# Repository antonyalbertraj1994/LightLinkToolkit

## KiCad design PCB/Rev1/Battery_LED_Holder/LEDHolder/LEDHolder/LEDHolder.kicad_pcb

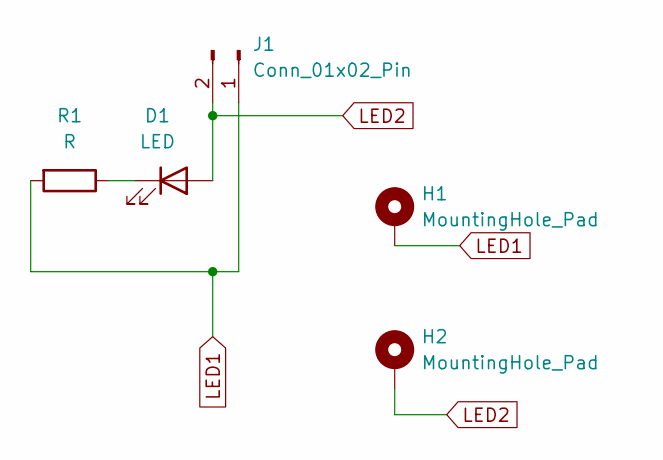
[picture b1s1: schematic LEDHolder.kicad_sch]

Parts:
D1: LED; LED_0805_2012Metric_Pad1.15x1.40mm_HandSolder
H1, H2: MountingHole_Pad; MT_Hole
J1: Conn_01x02_Pin; PinHeader_1x02_P2.54mm_Vertical
R1: R; R_0603_1608Metric_Pad0.98x0.95mm_HandSolder

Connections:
LED1: H1.1, J1.1, R1.2
LED2: D1.2 (A), H2.1, J1.2
unnamed: D1.1 (K), R1.1

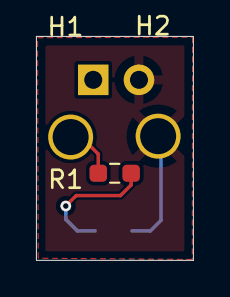
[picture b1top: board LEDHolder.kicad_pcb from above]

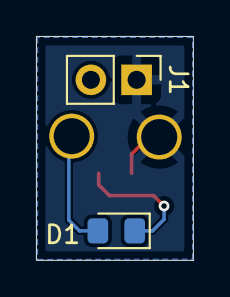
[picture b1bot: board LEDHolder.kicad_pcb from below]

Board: 2 copper layers, 8.7 x 12.4 mm, 5 parts (2 on the bottom side), 3 nets.

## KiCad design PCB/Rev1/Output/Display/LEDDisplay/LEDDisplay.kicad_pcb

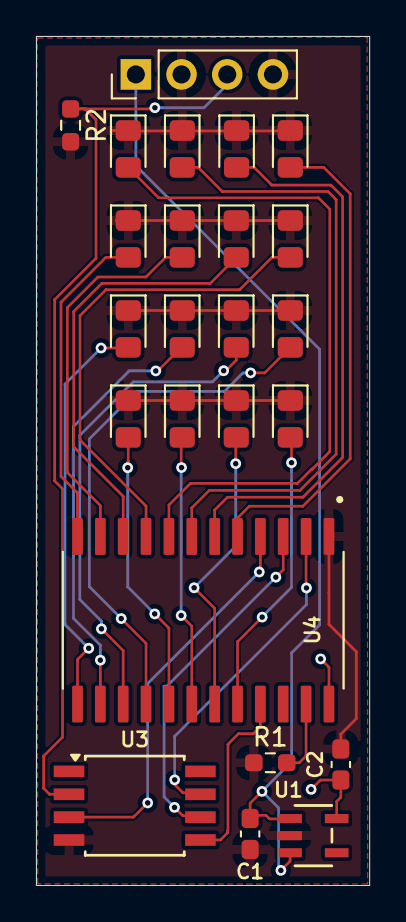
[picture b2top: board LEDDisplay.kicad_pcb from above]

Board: 2 copper layers, 18.5 x 47.2 mm, 24 parts (0 on the bottom side), 25 nets.

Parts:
C1, C2: C; C_0603_1608Metric_Pad1.08x0.95mm_HandSolder
D1, D2, D3, D4, D5, D6, D7, D8, D9, D10, D11, D12, D13, D14, D15, D16: LED; LED_0805_2012Metric_Pad1.15x1.40mm_HandSolder
J3: Conn_01x04_Pin; PinHeader_1x04_P2.54mm_Vertical
R1, R2: R; R_0603_1608Metric_Pad0.98x0.95mm_HandSolder
U1: MIC5504; SOT-23-5_MC_MCH
U3: ATtiny85; SOIC-8W_5.3x5.3mm_P1.27mm
U4: STP16CP05MTR; SOIC127P1032X265-24N

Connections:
BPW34_1: J3.3, R2.1, U3.2 (XTAL1/PB3)
CLK: U3.6 (PB1), U4.3 (CLK)
DATA: U3.7 (PB2), U4.2 (SDI)
GND: C1.2, C2.2, D1.1 (K), D2.1 (K), D3.1 (K), D4.1 (K), D5.1 (K), D6.1 (K), D7.1 (K), D8.1 (K), D9.1 (K), D10.1 (K), D11.1 (K), D12.1 (K), D13.1 (K), D14.1 (K), D15.1 (K), D16.1 (K), J3.2, J3.4, R1.1, R2.2, U1.2 (GND), U3.4 (GND), U4.1 (GND)
L1: D1.2 (A), U4.5 (~OUT0)
L2: D2.2 (A), U4.6 (~OUT1)
L3: D3.2 (A), U4.7 (~OUT2)
L4: D4.2 (A), U4.8 (~OUT3)
L5: D5.2 (A), U4.9 (~OUT4)
L6: D6.2 (A), U4.10 (~OUT5)
L7: D7.2 (A), U4.11 (~OUT6)
L8: D8.2 (A), U4.12 (~OUT7)
L9: D9.2 (A), U4.13 (~OUT8)
L10: D10.2 (A), U4.14 (~OUT9)
L11: D11.2 (A), U4.15 (~OUT10)
L12: D12.2 (A), U4.16 (~OUT11)
L13: D13.2 (A), U4.17 (~OUT12)
L14: D14.2 (A), U4.18 (~OUT13)
L15: D15.2 (A), U4.19 (~OUT14)
L16: D16.2 (A), U4.20 (~OUT15)
LE: U3.3 (XTAL2/PB4), U4.4 (LE/DM1)
unnamed: R1.2, U4.23 (R-EXT)
OE: U3.5 (AREF/PB0), U4.21 (~OE/DM2)
VCC: C1.1, J3.1, U1.1 (VIN), U1.3 (EN)
VDD_3.3V: C2.1, U1.5 (VOUT), U4.24 (VDD)

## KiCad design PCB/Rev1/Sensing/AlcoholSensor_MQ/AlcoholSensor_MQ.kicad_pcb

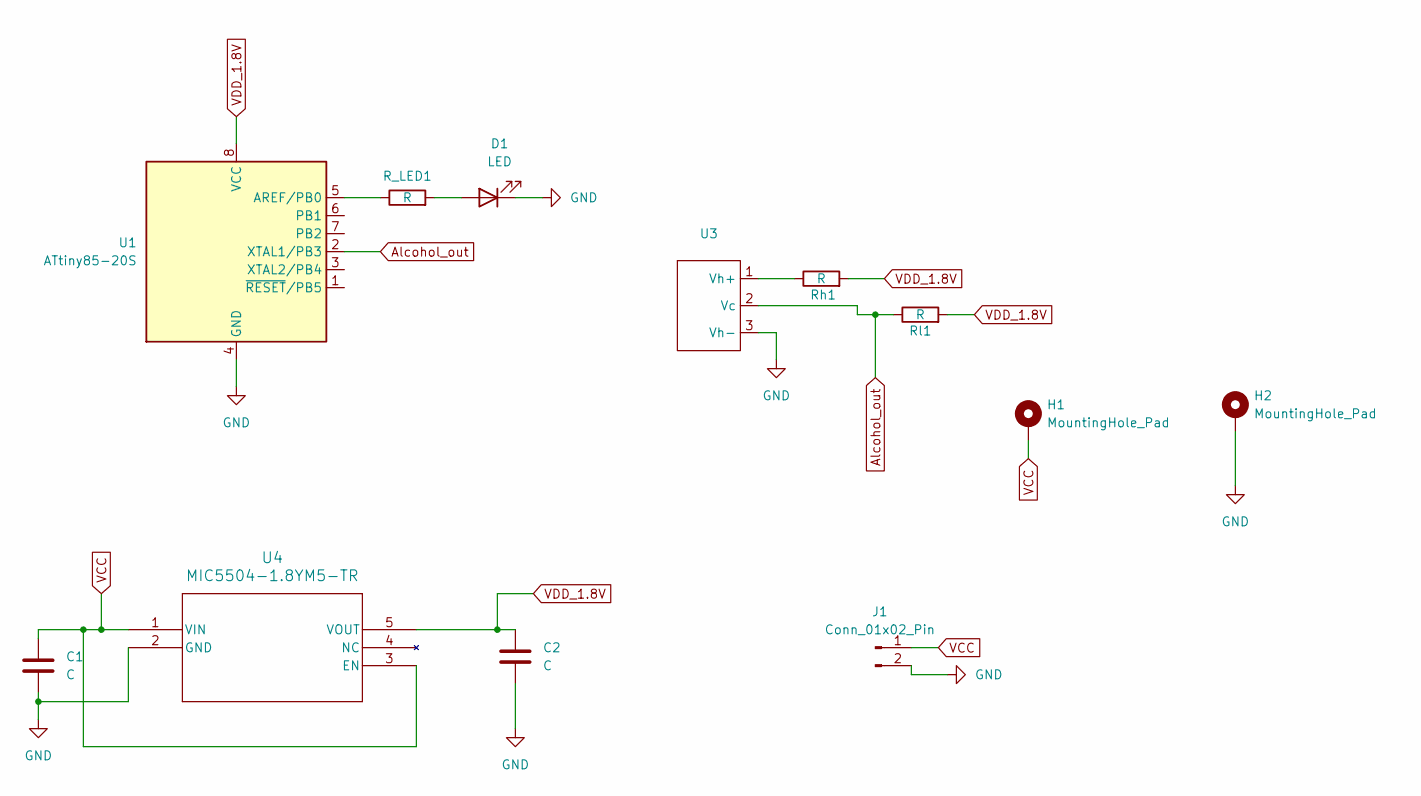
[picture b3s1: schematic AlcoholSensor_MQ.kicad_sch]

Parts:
C1, C2: C; C_0603_1608Metric_Pad1.08x0.95mm_HandSolder
D1: LED; LED_0805_2012Metric_Pad1.15x1.40mm_HandSolder
H1, H2: MountingHole_Pad; MT_Hole
J1: Conn_01x02_Pin; PinHeader_1x02_P2.54mm_Vertical
R_LED1: R; R_0603_1608Metric_Pad0.98x0.95mm_HandSolder
Rh1: R; R_0603_1608Metric_Pad0.98x0.95mm_HandSolder
Rl1: R; R_0603_1608Metric_Pad0.98x0.95mm_HandSolder
U1: ATtiny85-20S; SOIC-8W_5.3x5.3mm_P1.27mm
U3: MQ303
U4: MIC5504-1.8YM5-TR; SOT23-5LD-PL-1_MCH

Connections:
Alcohol_out: Rl1.1, U1.2 (XTAL1/PB3), U3.2 (Vc)
GND: C1.2, C2.2, D1.1 (K), H2.1, J1.2, U1.4 (GND), U3.3 (Vh-), U4.2 (GND)
unnamed: D1.2 (A), R_LED1.2
unnamed: R_LED1.1, U1.5 (AREF/PB0)
unnamed: Rh1.1, U3.1 (Vh+)
VCC: C1.1, H1.1, J1.1, U4.1 (VIN), U4.3 (EN)
VDD_1.8V: C2.1, Rh1.2, Rl1.2, U1.8 (VCC), U4.5 (VOUT)

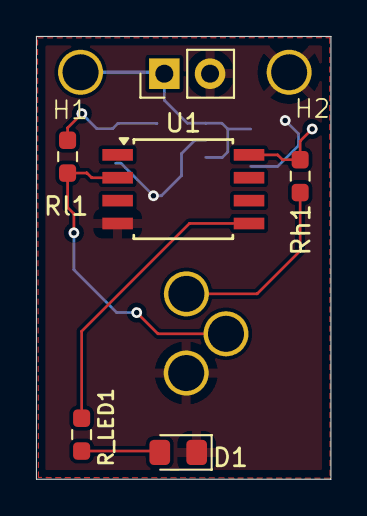
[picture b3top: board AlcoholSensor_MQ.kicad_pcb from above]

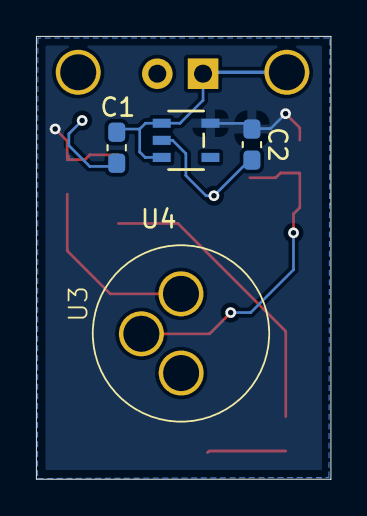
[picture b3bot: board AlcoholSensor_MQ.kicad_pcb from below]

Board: 2 copper layers, 16.4 x 24.6 mm, 12 parts (4 on the bottom side), 7 nets.

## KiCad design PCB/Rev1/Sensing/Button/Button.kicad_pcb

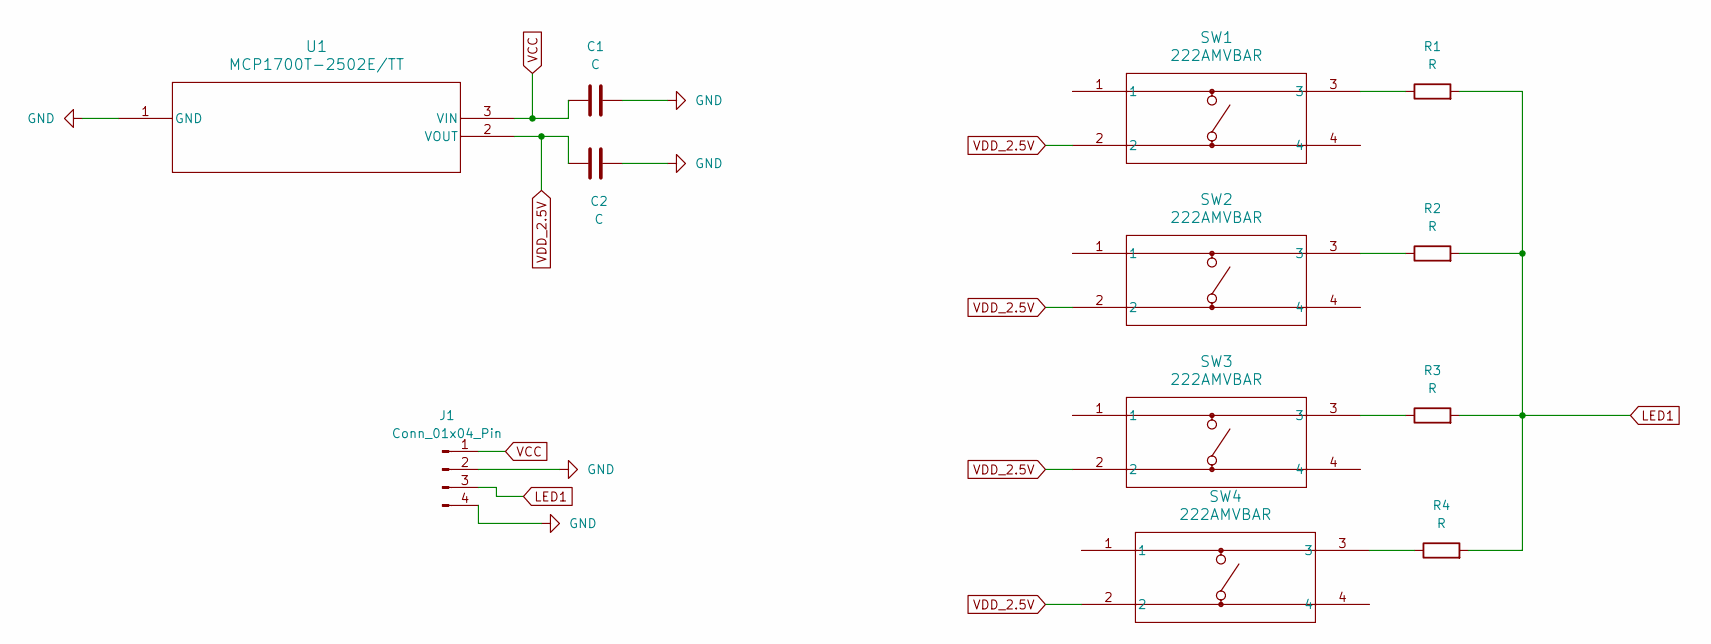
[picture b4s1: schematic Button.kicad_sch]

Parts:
C1, C2: C; C_0603_1608Metric
J1: Conn_01x04_Pin; PinHeader_1x04_P2.54mm_Vertical
R1, R2, R3, R4: R; R_0603_1608Metric
SW1, SW2, SW3, SW4: 222AMVBAR; SO4_222A-M-V-B_CTS
U1: MCP1700T-2502E/TT; SOT-23_MC_MCH

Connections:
GND: C1.2, C2.2, J1.2, J1.4, U1.1 (GND)
LED1: J1.3, R1.2, R2.2, R3.2, R4.2
unnamed: R1.1, SW1.3
unnamed: R2.1, SW2.3
unnamed: R3.1, SW3.3
unnamed: R4.1, SW4.3
VCC: C1.1, J1.1, U1.3 (VIN)
VDD_2.5V: C2.1, SW1.2, SW2.2, SW3.2, SW4.2, U1.2 (VOUT)

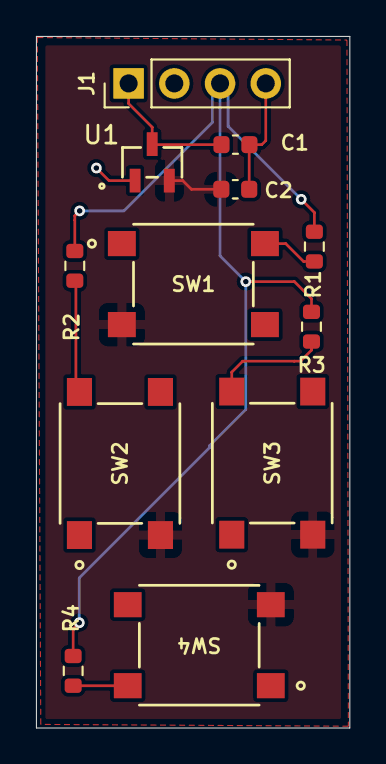
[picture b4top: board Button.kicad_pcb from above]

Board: 2 copper layers, 17.4 x 38.4 mm, 12 parts (0 on the bottom side), 8 nets.

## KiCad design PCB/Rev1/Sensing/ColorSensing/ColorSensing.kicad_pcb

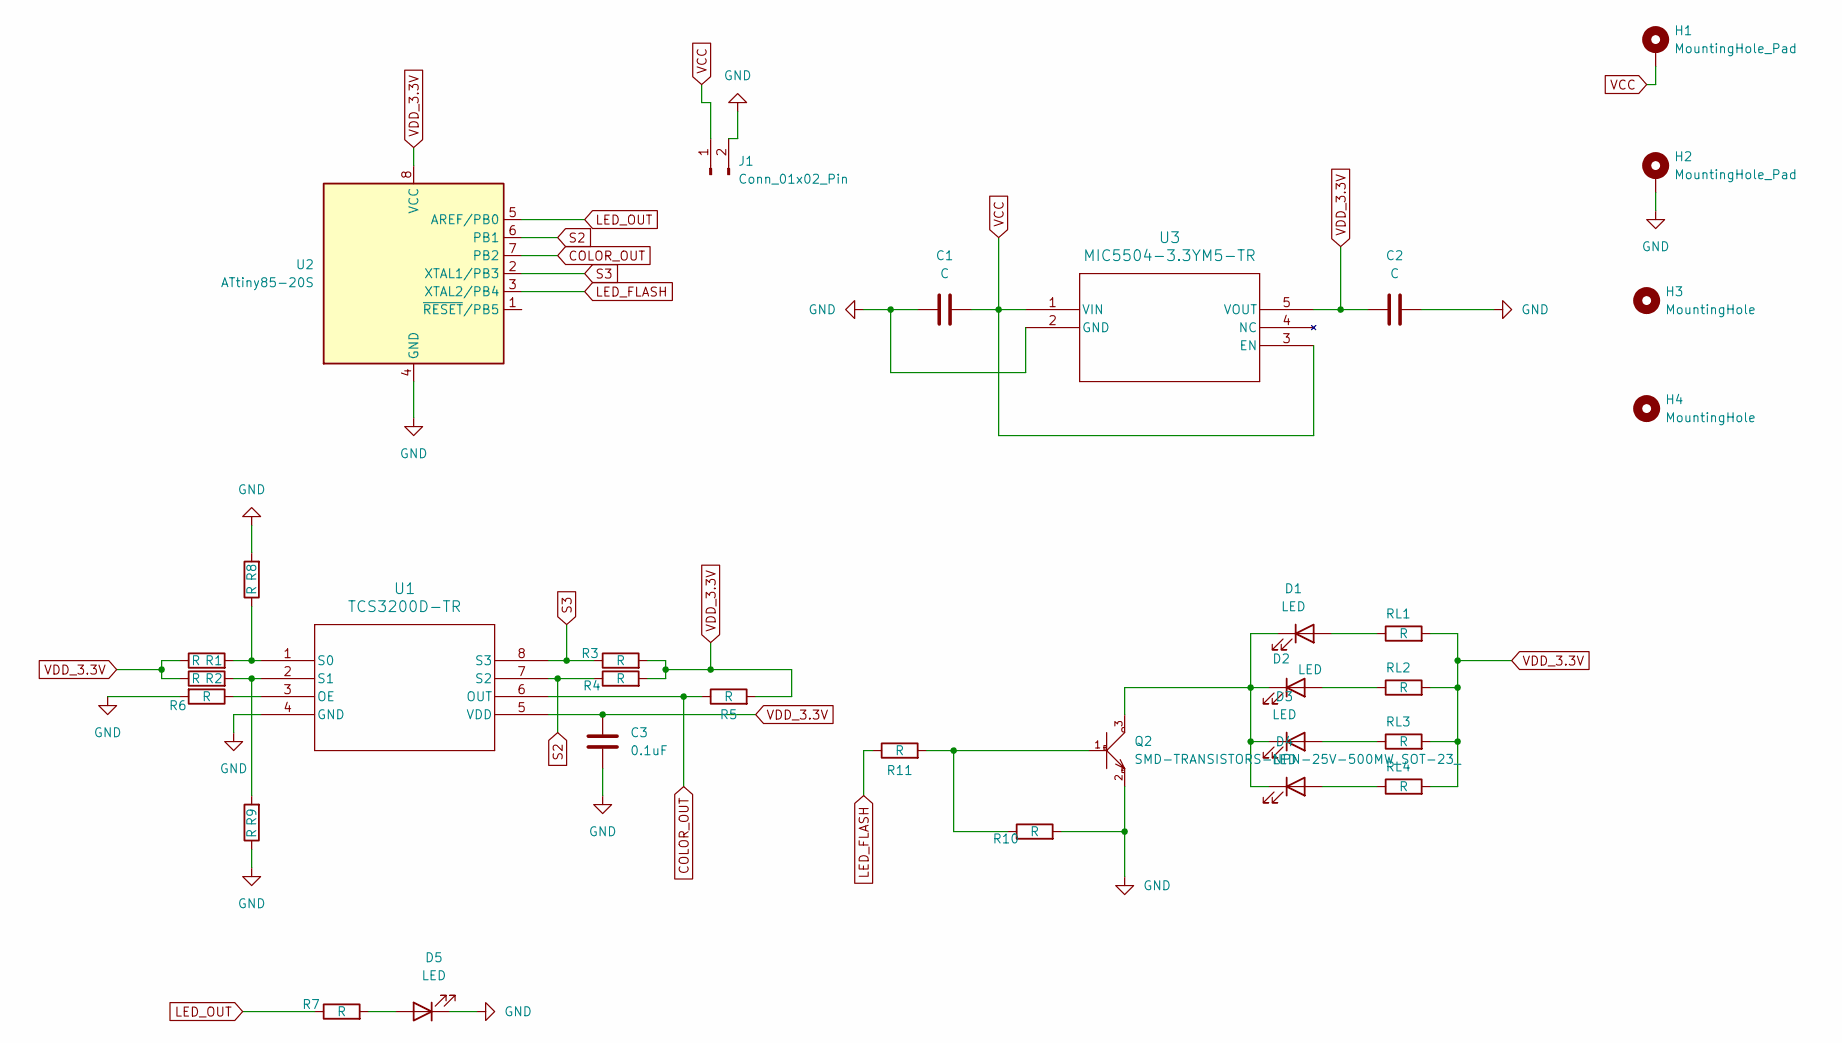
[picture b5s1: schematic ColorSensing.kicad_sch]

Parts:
C1, C2: C; C_0603_1608Metric_Pad1.08x0.95mm_HandSolder
C3: 0.1uF; C_0603_1608Metric_Pad1.08x0.95mm_HandSolder
D1, D2, D3, D4: LED; LED_D5.0mm
D5: LED; LED_0805_2012Metric_Pad1.15x1.40mm_HandSolder
H1, H2: MountingHole_Pad; MT_Hole
H3, H4: MountingHole; MT_Hole
J1: Conn_01x02_Pin; PinHeader_1x02_P2.54mm_Vertical
Q2: SMD-TRANSISTORS-NPN-25V-500MW_SOT-23_; SOT-23; MPN S8050
R1, R2, R3, R4, R5, R6, R7, R8, R9, R10, R11: R; R_0603_1608Metric_Pad0.98x0.95mm_HandSolder
RL1, RL2, RL3, RL4: R; R_0603_1608Metric_Pad0.98x0.95mm_HandSolder
U1: TCS3200D-TR; SO_3200D-TR_AMS
U2: ATtiny85-20S; SOIC-8W_5.3x5.3mm_P1.27mm
U3: MIC5504-3.3YM5-TR; SOT-23-5_MC_MCH

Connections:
COLOR_OUT: R5.1, U1.6 (OUT), U2.7 (PB2)
GND: C1.1, C2.2, C3.1, D5.1 (K), H2.1, J1.2, Q2.2, R6.2, R8.2, R9.1, R10.2, U1.4 (GND), U2.4 (GND), U3.2 (GND)
LED_FLASH: R11.1, U2.3 (XTAL2/PB4)
LED_OUT: R7.1, U2.5 (AREF/PB0)
unnamed: D1.2 (A), RL1.1
unnamed: D1.1 (K), D2.1 (K), D3.1 (K), D4.1 (K), Q2.3
unnamed: D2.2 (A), RL2.1
unnamed: D3.2 (A), RL3.1
unnamed: D4.2 (A), RL4.1
unnamed: D5.2 (A), R7.2
unnamed: Q2.1, R10.1, R11.2
unnamed: R6.1, U1.3 (OE)
unnamed: R1.2, R8.1, U1.1 (S0)
unnamed: R2.2, R9.2, U1.2 (S1)
S2: R4.1, U1.7 (S2), U2.6 (PB1)
S3: R3.1, U1.8 (S3), U2.2 (XTAL1/PB3)
VCC: C1.2, H1.1, J1.1, U3.1 (VIN), U3.3 (EN)
VDD_3.3V: C2.1, C3.2, R1.1, R2.1, R3.2, R4.2, R5.2, RL1.2, RL2.2, RL3.2, RL4.2, U1.5 (VDD), U2.8 (VCC), U3.5 (VOUT)

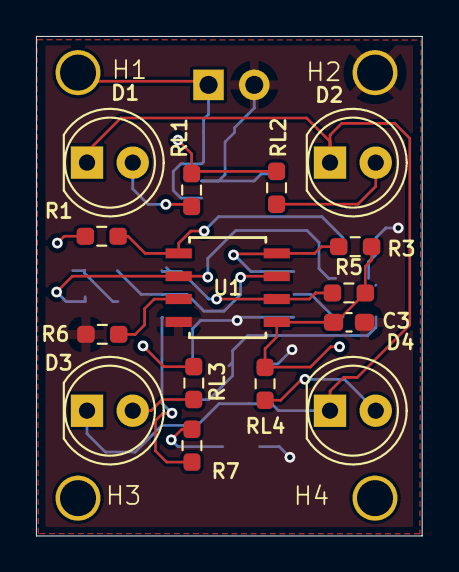
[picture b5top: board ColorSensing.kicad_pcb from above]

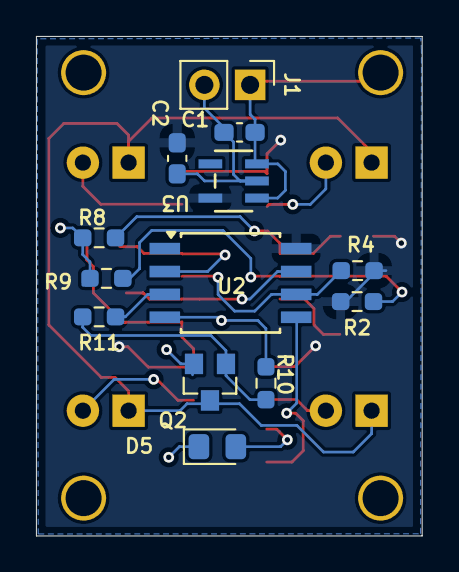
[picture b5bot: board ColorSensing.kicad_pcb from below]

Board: 2 copper layers, 21.4 x 27.8 mm, 32 parts (13 on the bottom side), 18 nets.

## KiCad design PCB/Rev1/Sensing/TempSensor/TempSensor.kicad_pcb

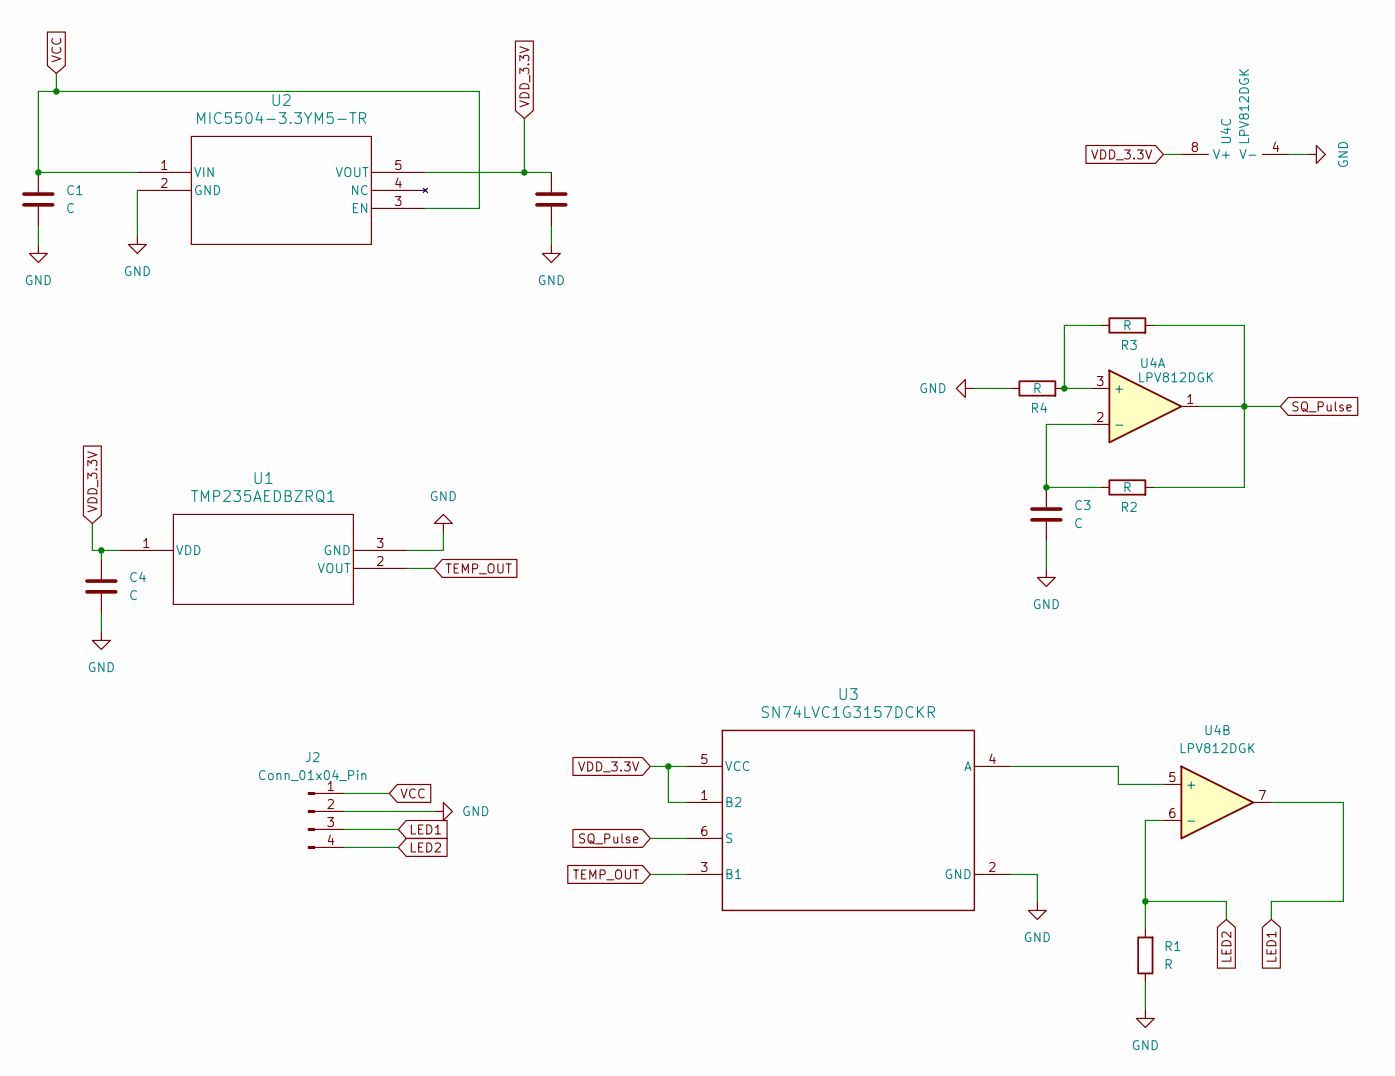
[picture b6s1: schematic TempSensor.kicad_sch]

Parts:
C1, C2, C3, C4: C; C_0603_1608Metric_Pad1.08x0.95mm_HandSolder
J2: Conn_01x04_Pin; PinHeader_1x04_P2.54mm_Vertical
R1, R2, R3, R4: R; R_0603_1608Metric_Pad0.98x0.95mm_HandSolder
U1: TMP235AEDBZRQ1; SOT-23_DBZ_TEX
U2: MIC5504-3.3YM5-TR; SOT-23-5_MC_MCH
U3: SN74LVC1G3157DCKR; DBV6
U4: LPV812DGK; VSSOP-8_3.0x3.0mm_P0.65mm

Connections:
GND: C1.2, C2.2, C3.2, C4.2, J2.2, R1.1, R4.1, U1.3 (GND), U2.2 (GND), U3.2 (GND), U4.4 (V-)
LED1: J2.3, U4.7
LED2: J2.4, R1.2, U4.6 (-)
unnamed: U3.4 (A), U4.5 (+)
unnamed: R3.1, R4.2, U4.3 (+)
unnamed: C3.1, R2.1, U4.2 (-)
SQ_Pulse: R2.2, R3.2, U3.6 (S), U4.1
TEMP_OUT: U1.2 (VOUT), U3.3 (B1)
VCC: C1.1, J2.1, U2.1 (VIN), U2.3 (EN)
VDD_3.3V: C2.1, C4.1, U1.1 (VDD), U2.5 (VOUT), U3.1 (B2), U3.5 (VCC), U4.8 (V+)

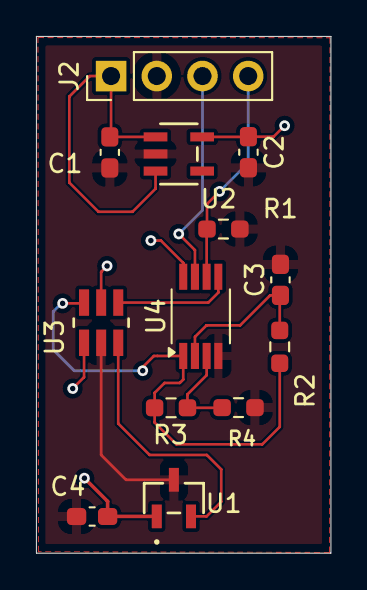
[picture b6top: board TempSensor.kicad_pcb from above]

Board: 2 copper layers, 16.4 x 28.7 mm, 13 parts (0 on the bottom side), 10 nets.

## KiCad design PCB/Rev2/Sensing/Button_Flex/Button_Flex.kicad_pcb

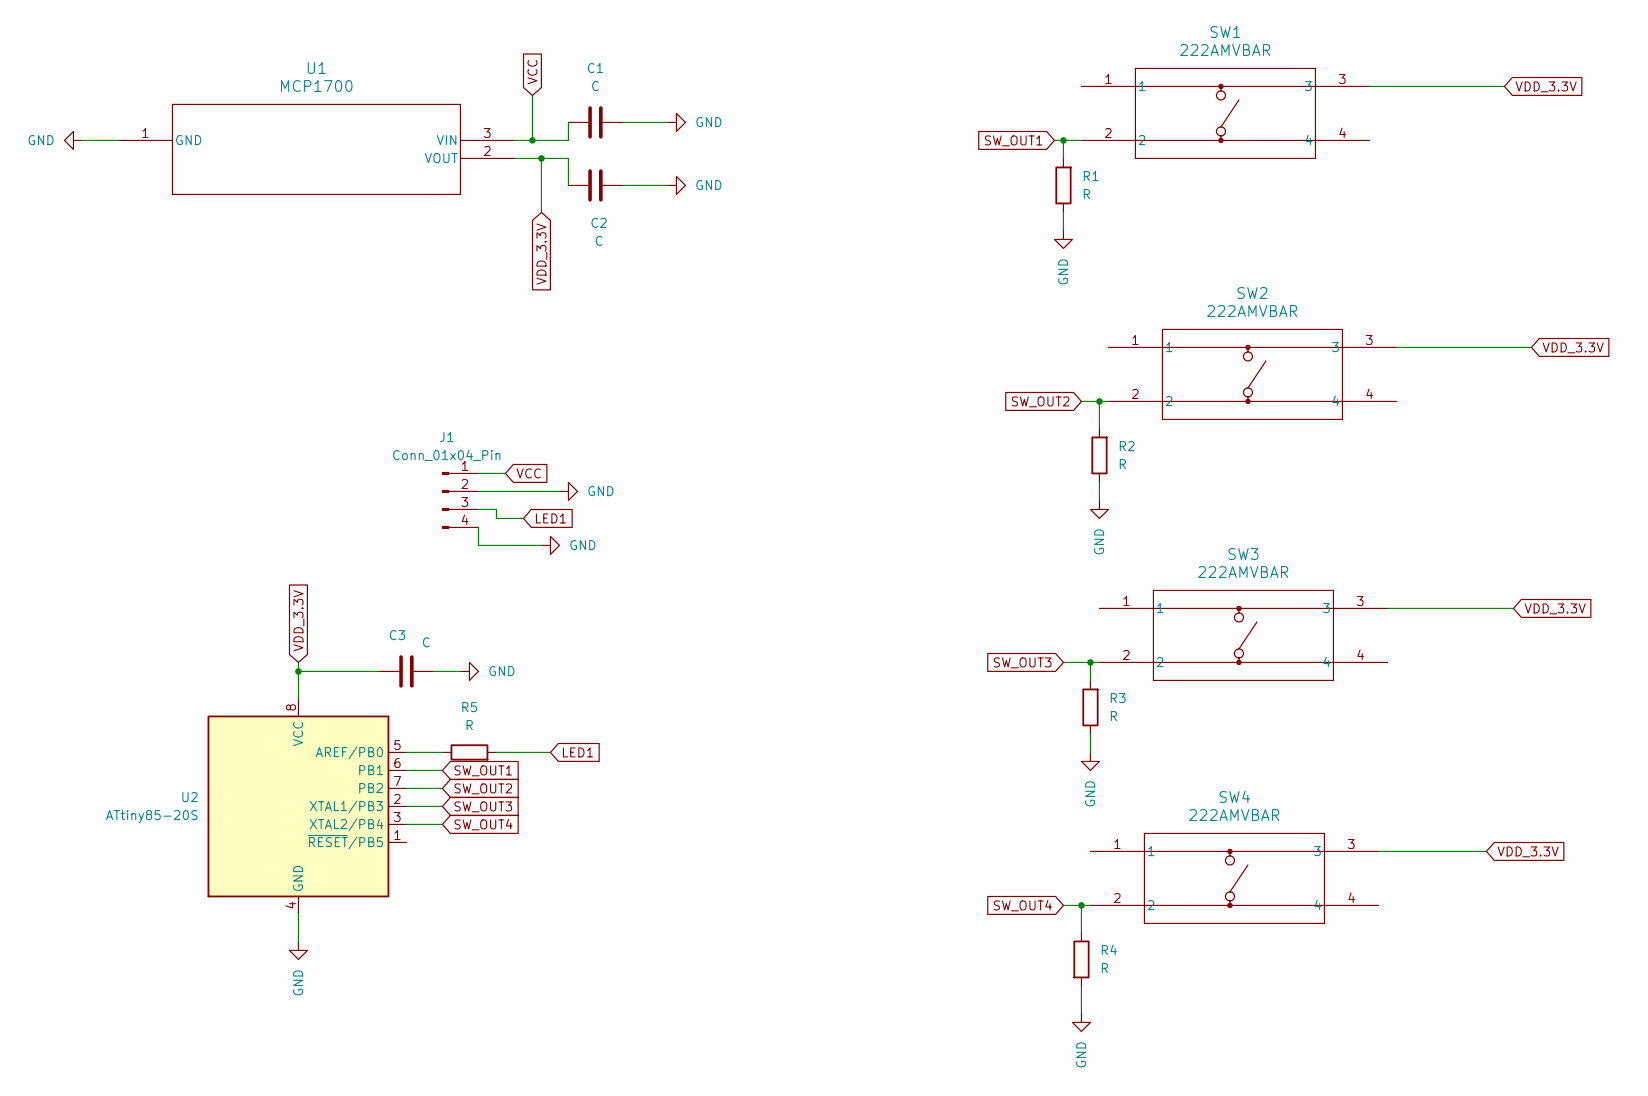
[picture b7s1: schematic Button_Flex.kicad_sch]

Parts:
C1, C2, C3: C; C_0603_1608Metric
J1: Conn_01x04_Pin; PinHeader_1x04_P2.54mm_Vertical
R1, R2, R3, R4, R5: R; R_0603_1608Metric
SW1, SW2, SW3, SW4: 222AMVBAR; SO4_222A-M-V-B_CTS
U1: MCP1700; SOT-23_MC_MCH
U2: ATtiny85-20S; SOIC-8W_5.3x5.3mm_P1.27mm

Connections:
GND: C1.2, C2.2, C3.2, J1.2, J1.4, R1.1, R2.1, R3.1, R4.2, U1.1 (GND), U2.4 (GND)
LED1: J1.3, R5.2
unnamed: R5.1, U2.5 (AREF/PB0)
SW_OUT1: R1.2, SW1.2, U2.6 (PB1)
SW_OUT2: R2.2, SW2.2, U2.7 (PB2)
SW_OUT3: R3.2, SW3.2, U2.2 (XTAL1/PB3)
SW_OUT4: R4.1, SW4.2, U2.3 (XTAL2/PB4)
VCC: C1.1, J1.1, U1.3 (VIN)
VDD_3.3V: C2.1, C3.1, SW1.3, SW2.3, SW3.3, SW4.3, U1.2 (VOUT), U2.8 (VCC)

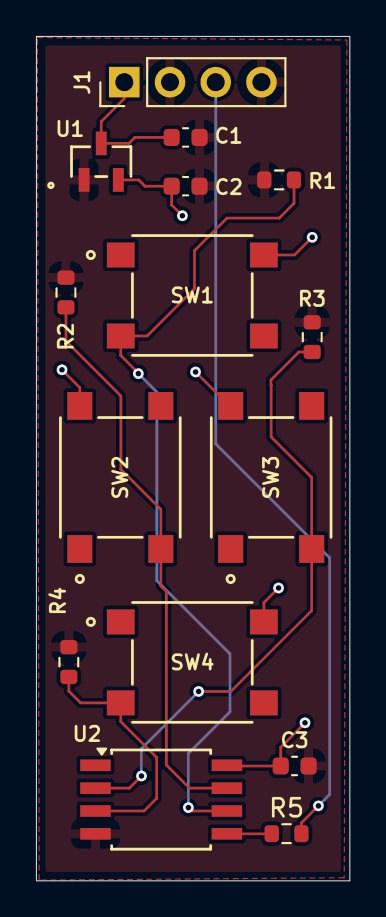
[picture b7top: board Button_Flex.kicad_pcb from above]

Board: 2 copper layers, 17.4 x 46.9 mm, 15 parts (0 on the bottom side), 9 nets.
